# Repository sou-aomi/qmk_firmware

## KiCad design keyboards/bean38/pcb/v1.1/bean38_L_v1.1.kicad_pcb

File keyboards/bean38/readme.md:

# Bean38

*A short description of the keyboard/project*

* Keyboard Maintainer: [sou-aomi](https://github.com/sou-aomi)/ [@sou_aomi](https://twitter.com/sou_aomi)
* Hardware Supported: Bean38 PCB, Pro micro
* Hardware Availability: https://github.com/sou-aomi/Bean38

Make example for this keyboard (after setting up your build environment):

    make bean38:default

See the [build environment setup](https://docs.qmk.fm/#/getting_started_build_tools) and the [make instructions](https://docs.qmk.fm/#/getting_started_make_guide) for more information. Brand new to QMK? Start with our [Complete Newbs Guide](https://docs.qmk.fm/#/newbs).

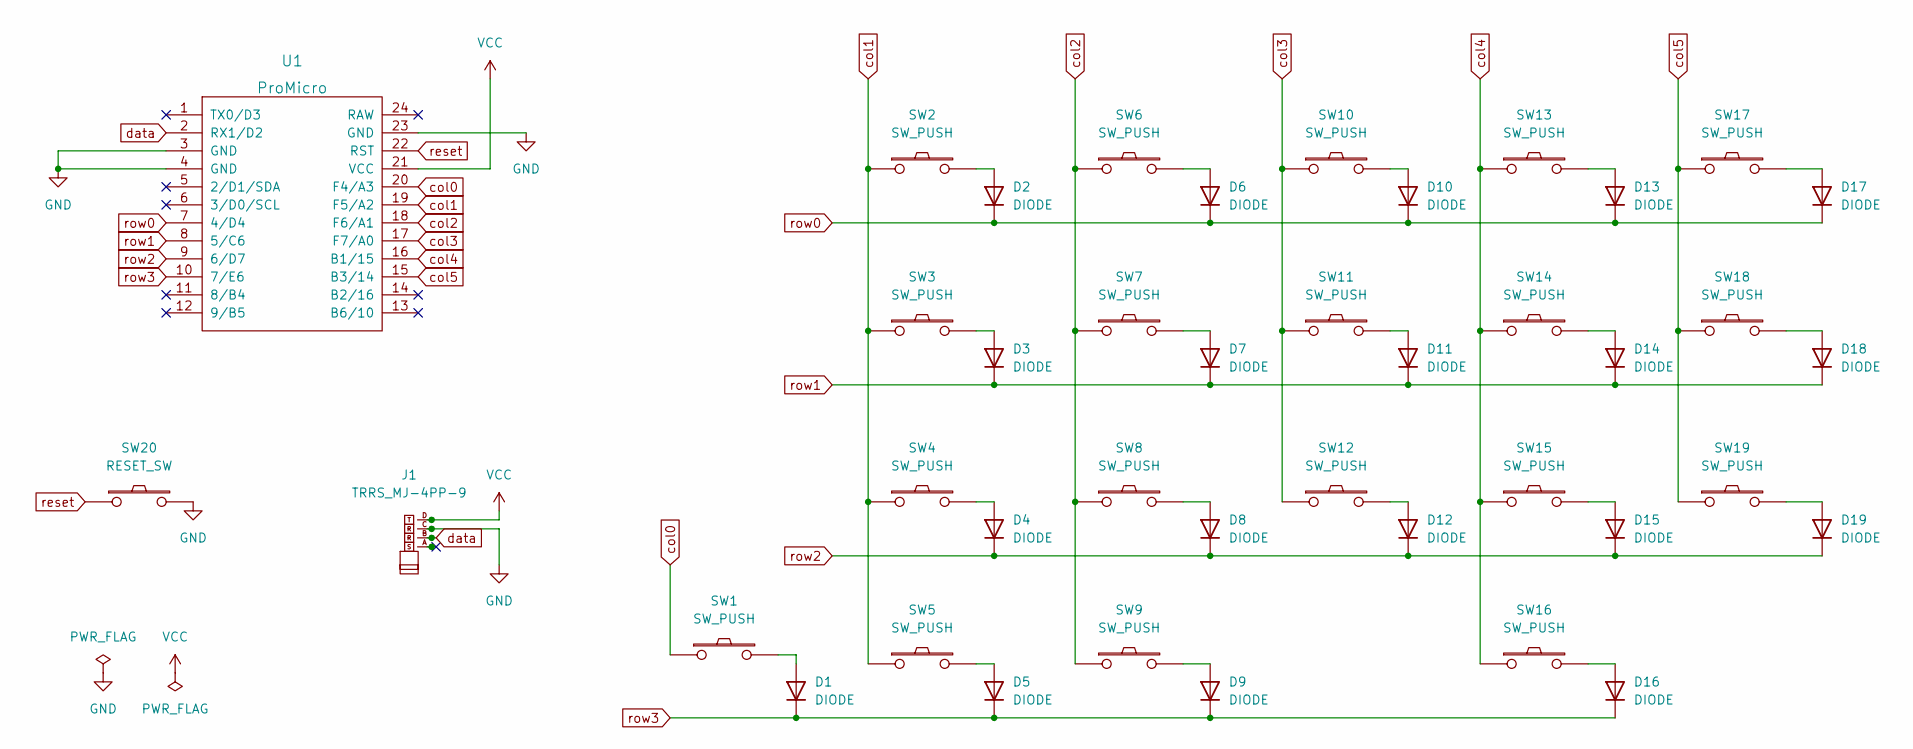
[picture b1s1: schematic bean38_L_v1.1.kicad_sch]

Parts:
D1, D2, D3, D4, D5, D6, D7, D8, D9, D10, D11, D12, D13, D14, D15, D16, D17, D18, D19: DIODE; D3_SMD_v2
J1: TRRS_MJ-4PP-9; MJ-4PP-9_1side
SW1, SW2, SW3, SW4, SW5, SW6, SW7, SW8, SW9, SW10, SW11, SW12, SW13, SW14, SW15, SW16, SW17, SW18, SW19: SW_PUSH; CherryMX_Hotswap
SW20: RESET_SW; ResetSW_1side
U1: ProMicro; ProMicro_v2_1side

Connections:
GND: J1.C, SW20.2, U1.3 (GND), U1.4 (GND), U1.23 (GND)
unnamed: D1.1 (A), SW1.2
unnamed: D2.1 (A), SW2.2
unnamed: D3.1 (A), SW3.2
unnamed: D4.1 (A), SW4.2
unnamed: D5.1 (A), SW5.2
unnamed: D6.1 (A), SW6.2
unnamed: D7.1 (A), SW7.2
unnamed: D8.1 (A), SW8.2
unnamed: D9.1 (A), SW9.2
unnamed: D10.1 (A), SW10.2
unnamed: D11.1 (A), SW11.2
unnamed: D12.1 (A), SW12.2
unnamed: D13.1 (A), SW13.2
unnamed: D14.1 (A), SW14.2
unnamed: D15.1 (A), SW15.2
unnamed: D16.1 (A), SW16.2
unnamed: D17.1 (A), SW17.2
unnamed: D18.1 (A), SW18.2
unnamed: D19.1 (A), SW19.2
VCC: J1.D, U1.21 (VCC)
col0: SW1.1, U1.20 (F4/A3)
col1: SW2.1, SW3.1, SW4.1, SW5.1, U1.19 (F5/A2)
col2: SW6.1, SW7.1, SW8.1, SW9.1, U1.18 (F6/A1)
col3: SW10.1, SW11.1, SW12.1, U1.17 (F7/A0)
col4: SW13.1, SW14.1, SW15.1, SW16.1, U1.16 (B1/15)
col5: SW17.1, SW18.1, SW19.1, U1.15 (B3/14)
data: J1.B, U1.2 (RX1/D2)
reset: SW20.1, U1.22 (RST)
row0: D2.2 (K), D6.2 (K), D10.2 (K), D13.2 (K), D17.2 (K), U1.7 (4/D4)
row1: D3.2 (K), D7.2 (K), D11.2 (K), D14.2 (K), D18.2 (K), U1.8 (5/C6)
row2: D4.2 (K), D8.2 (K), D12.2 (K), D15.2 (K), D19.2 (K), U1.9 (6/D7)
row3: D1.2 (K), D5.2 (K), D9.2 (K), D16.2 (K), U1.10 (7/E6)

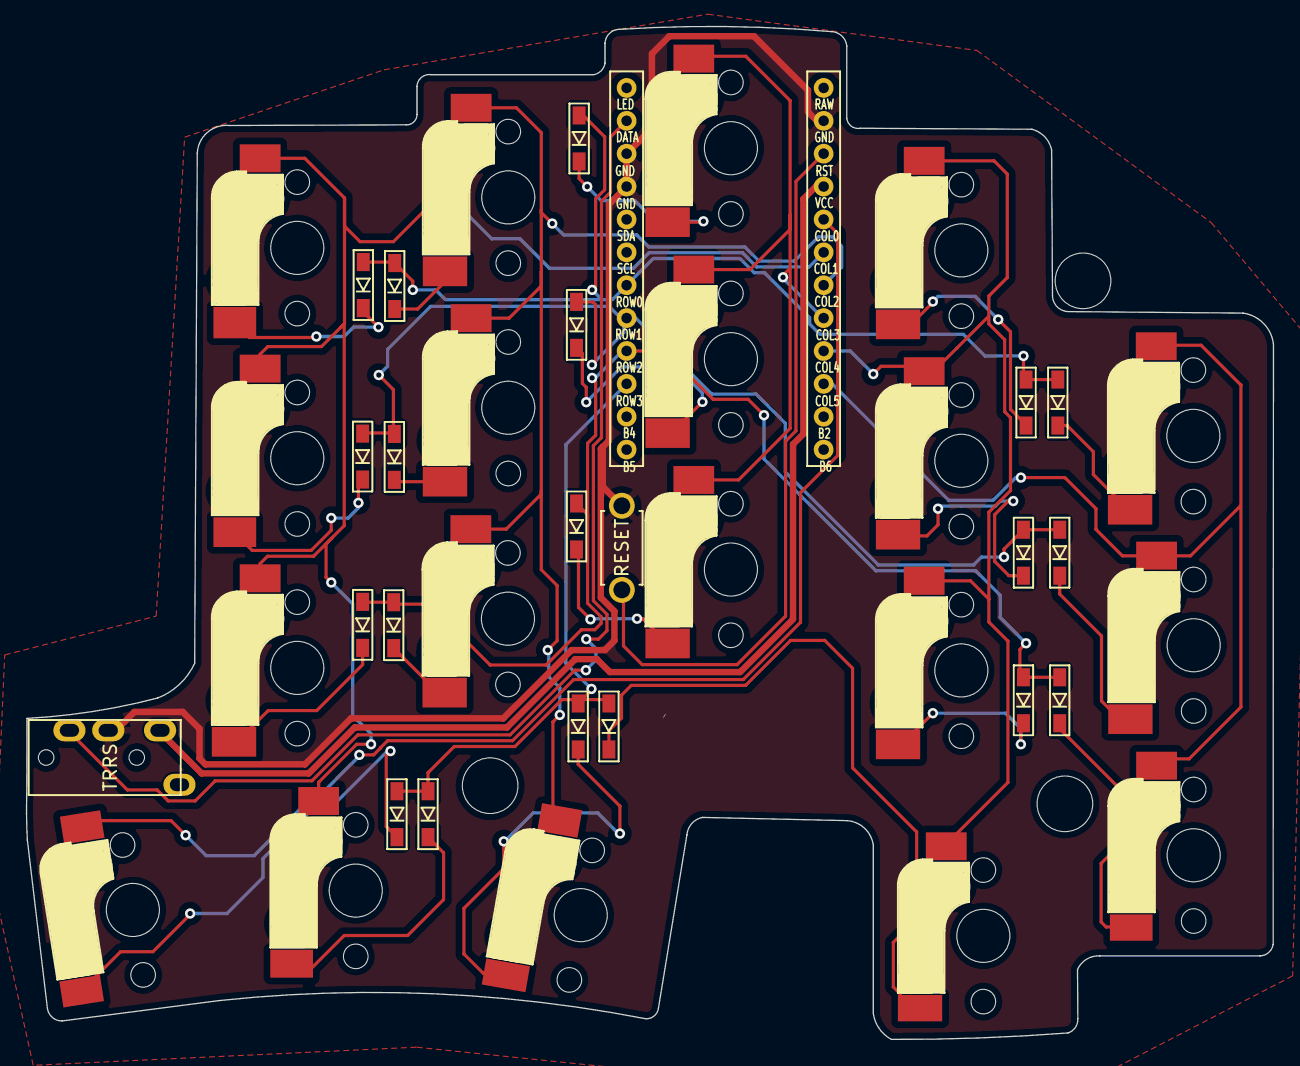
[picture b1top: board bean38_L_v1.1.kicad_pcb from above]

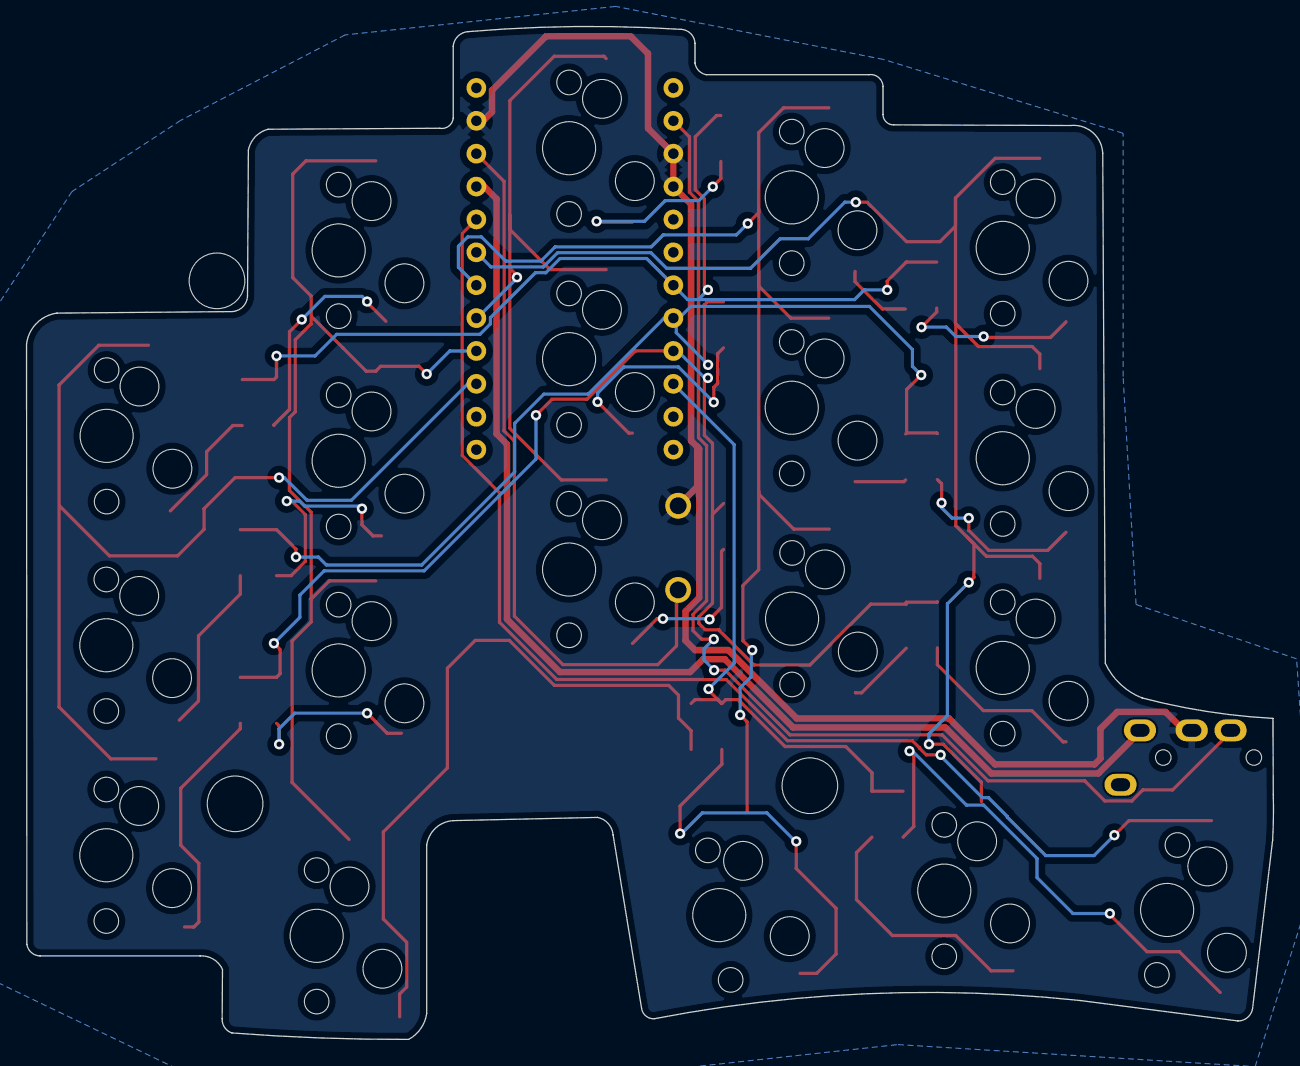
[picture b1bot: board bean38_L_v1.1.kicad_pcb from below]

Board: 2 copper layers, 96.3 x 78.2 mm, 43 parts (20 on the bottom side), 33 nets.

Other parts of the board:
Ref**: Val**; M2_HOLE_v2
Ref**#2: Val**; M2_HOLE_v2

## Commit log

2023-02-13 add bean38 files
2023-02-13 Fix readme.md
